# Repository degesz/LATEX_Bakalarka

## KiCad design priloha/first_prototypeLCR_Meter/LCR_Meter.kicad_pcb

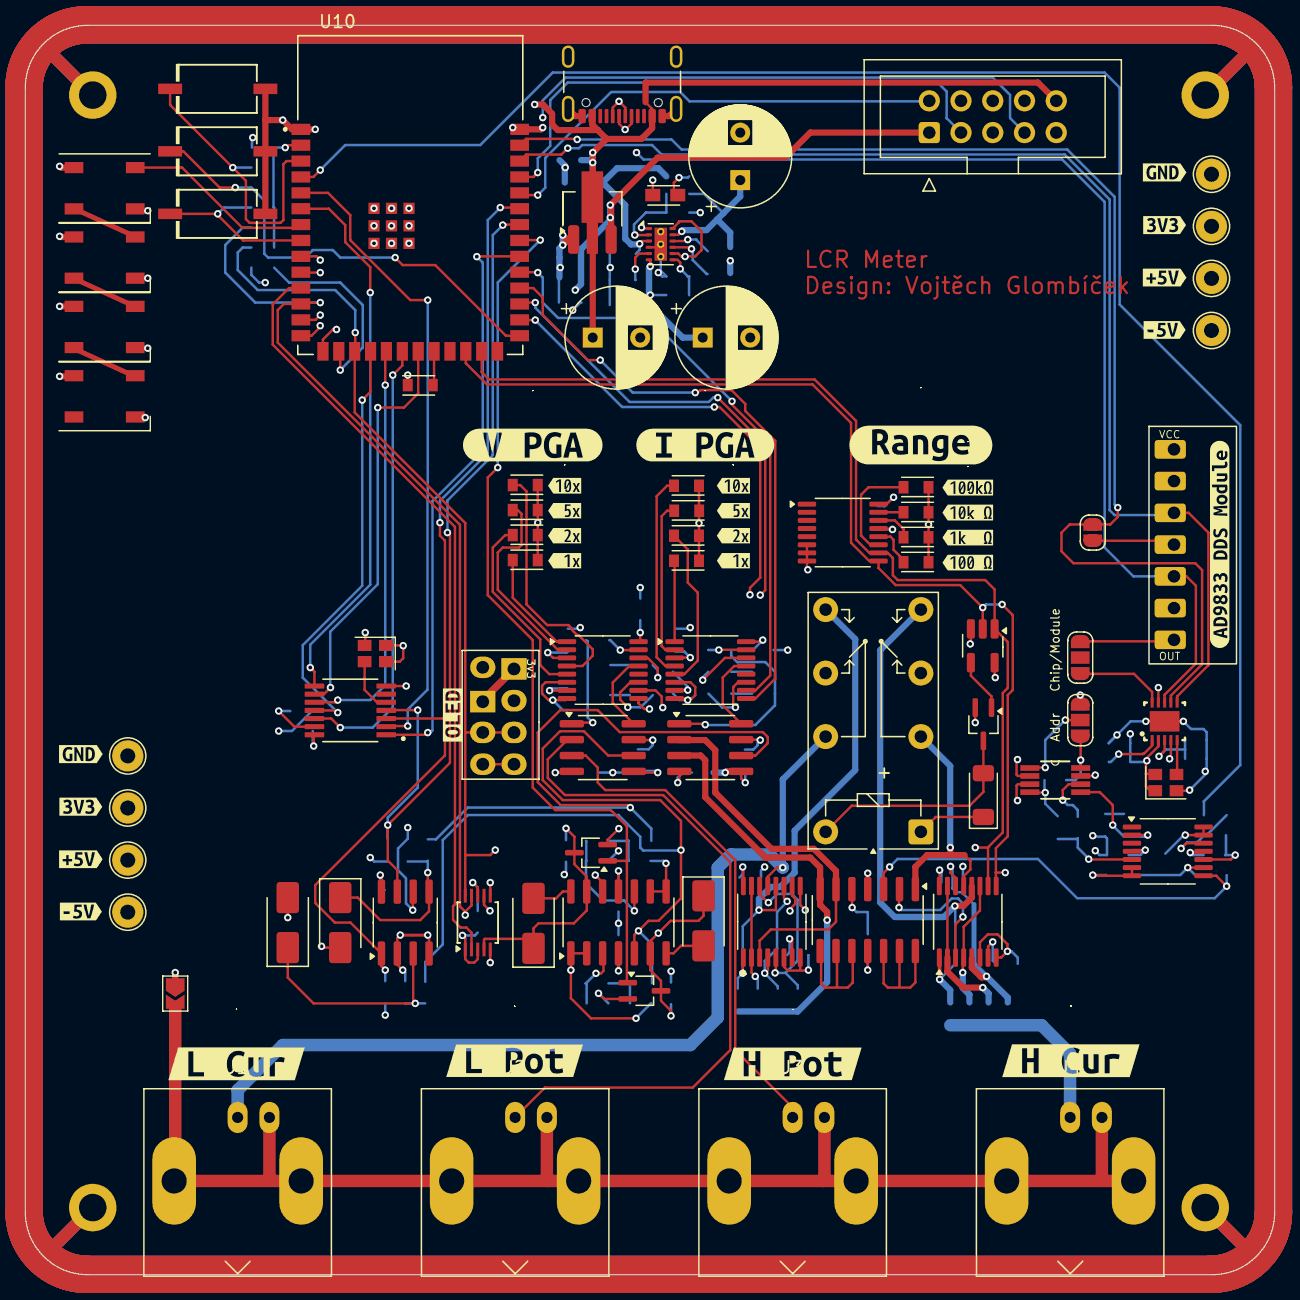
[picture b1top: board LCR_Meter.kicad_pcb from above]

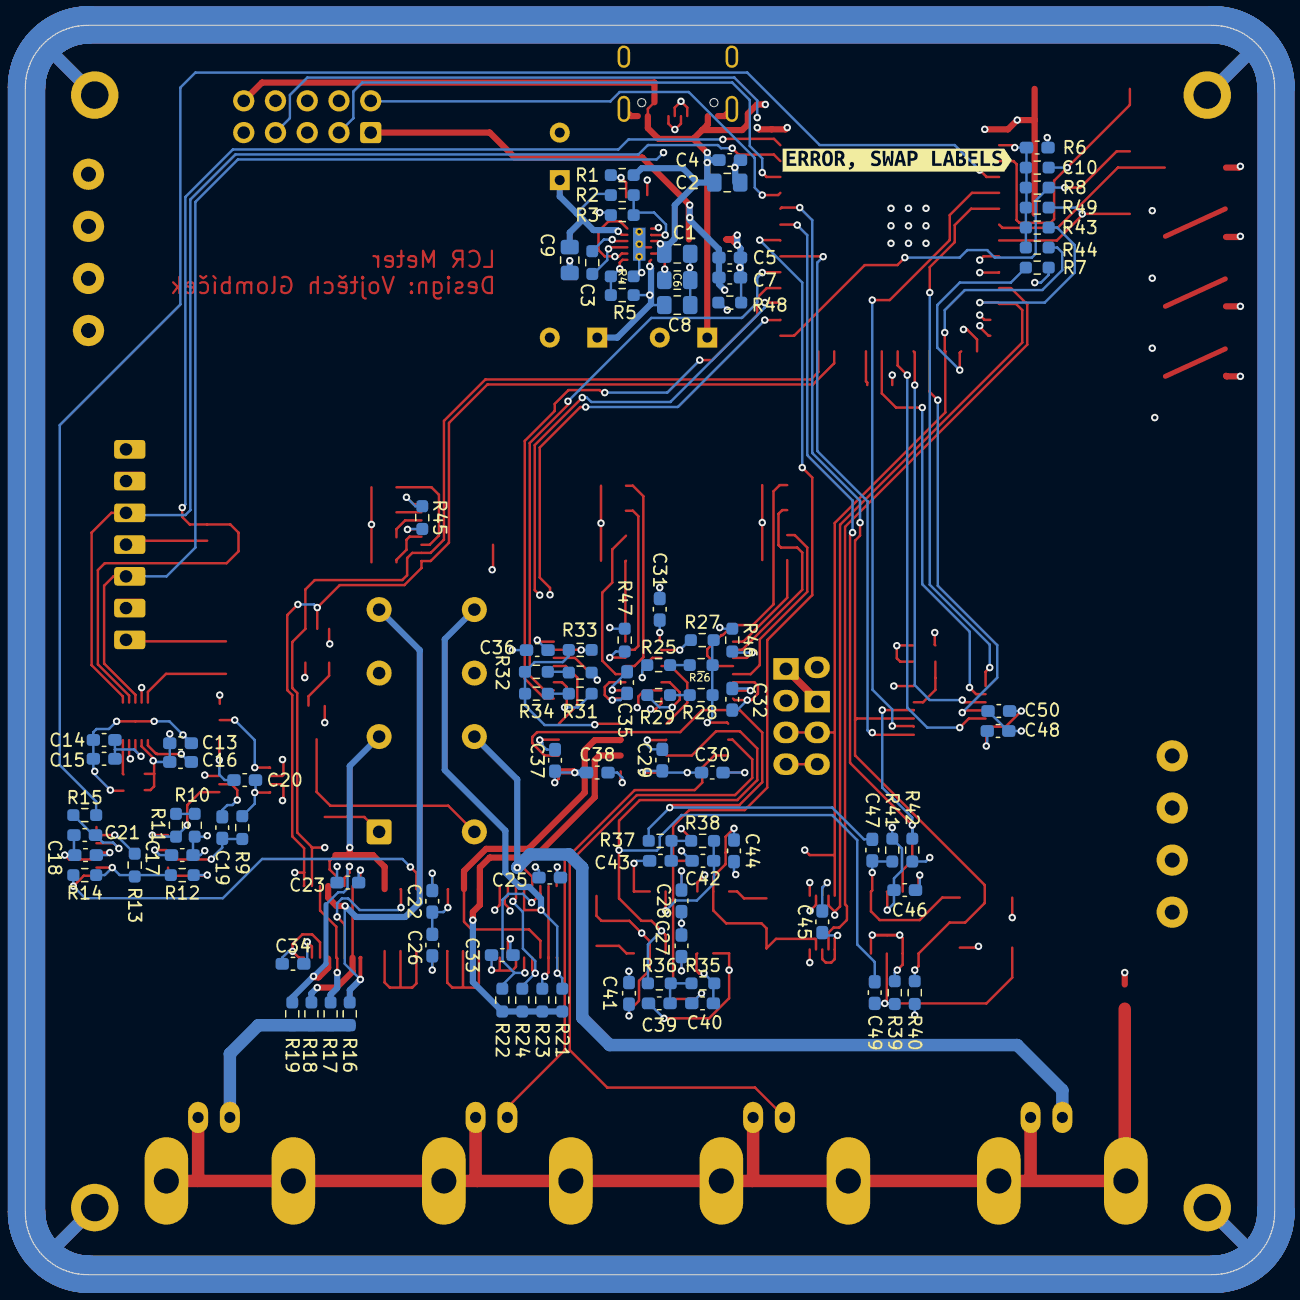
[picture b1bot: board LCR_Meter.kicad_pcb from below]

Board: 6 copper layers, 99.9 x 99.9 mm, 198 parts (96 on the bottom side), 132 nets.

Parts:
 : TestPoint_THTPad_D2.5mm_Drill1.2mm
 #2,  #16: G***; kibuzzard-678FA578
 #3,  #4,  #5,  #6,  #7,  #10,  #14: TestPoint_THTPad_D2.5mm_Drill1.2mm
 #8,  #15: G***; kibuzzard-678FA580
 #9,  #11: G***; kibuzzard-678FA556
 #12,  #13: G***; kibuzzard-678FA586
C1, C2, C6, C8, C9: 4.7u; C_0805_2012Metric_Pad1.18x1.45mm_HandSolder
C3: 1u; R_0603_1608Metric_Pad0.98x0.95mm_HandSolder
C4, C5, C14, C19, C47, C49: 100n; C_0603_1608Metric_Pad1.08x0.95mm_HandSolder
C7, C10, C13, C15, C17, C18, C20, C21, C22, C23, C25, C26, C27, C28, C29, C30, C31, C32, C33, C34, C35, C36, C37, C38, C41, C44, C45, C46, C48, C50: 1u; C_0603_1608Metric_Pad1.08x0.95mm_HandSolder
C11, C12, C51: 470u; CP_Radial_D8.0mm_P3.80mm
C16: 10n; C_0603_1608Metric_Pad1.08x0.95mm_HandSolder
C39, C40, C42, C43: 330n; C_0603_1608Metric_Pad1.08x0.95mm_HandSolder
D1: LED; LED_miniPLCC_2315_Handsoldering
D2: D_Schottky; D_MiniMELF
D3, D4, D5, D6: SS14; D_SMA
D7, D8, D9, D10, D11, D12, D13, D14, D15, D16, D17, D18, D20: LED; LED_miniPLCC_2315
D19, D21, D22, D23: WS2812B; LED_WS2812B_PLCC4_5.0x5.0mm_P3.2mm
J1, J2, J3, J4: Conn_Coaxial; BNC_Amphenol_B6252HB-NPP3G-50_Horizontal
J5: USB_C_Receptacle_USB2.0_16P; USB_C_Receptacle_GCT_USB4105-xx-A_16P_TopMnt_Horizontal
J6: IDC 2x5; IDC-Header_2x05_P2.54mm_Vertical
J7: Display OLED; FanPinHeader_1x04_P2.54mm_Vertical
JP1, JP2: SolderJumper_3_Open; SolderJumper-3_P1.3mm_Open_RoundedPad1.0x1.5mm
JP3: SolderJumper_2_Open; SolderJumper-2_P1.3mm_Open_RoundedPad1.0x1.5mm
JP4: SolderJumper_2_Open; SolderJumper-2_P1.3mm_Open_TrianglePad1.0x1.5mm
K1: Relay_DPDT; Relay_CIT-J104D
Q1, Q2, Q3: NX3008NBK; SOT-323_SC-70_Handsoldering
R1, R6, R7, R8, R19, R22, R40, R42, R45, R46, R47, R48, R49: 1k; R_0603_1608Metric_Pad0.98x0.95mm_HandSolder
R2, R5, R43, R44: 4k7; R_0603_1608Metric_Pad0.98x0.95mm_HandSolder
R3, R4: 1k5; R_0603_1608Metric_Pad0.98x0.95mm_HandSolder
R9, R15, R17, R24, R27, R33, R39, R41: 100k; R_0603_1608Metric_Pad0.98x0.95mm_HandSolder
R10, R12, R13, R14, R18, R23, R35, R36, R37, R38: 10k; R_0603_1608Metric_Pad0.98x0.95mm_HandSolder
R11: 33k; R_0603_1608Metric_Pad0.98x0.95mm_HandSolder
R16, R21: 100R; R_0603_1608Metric_Pad0.98x0.95mm_HandSolder
R25, R29, R30, R31: 0R; R_0603_1608Metric_Pad0.98x0.95mm_HandSolder
R26, R32: 200k; R_0603_1608Metric_Pad0.98x0.95mm_HandSolder
R28, R34: 22k; R_0603_1608Metric_Pad0.98x0.95mm_HandSolder
SW1, SW2, SW3: SW_SPST; SW-SMD_L6.1-W3.7-LS7.9
U1: AD9837; AD9837_AD9837
U2, U5: TLV9154; SOIC-14_3.9x8.7mm_P1.27mm
U3: ADS1115IDGS; TSSOP-10_3x3mm_P0.5mm
U4: LM393; SOIC-8_3.9x4.9mm_P1.27mm
U7: TDC7200PWR; TDC7200PWR_SOP65P640X120-14N
U8: LM27762; WSON-12-1EP_3x2mm_P0.5mm_EP1x2.65_ThermalVias
U9: HT75xx-1-SOT89; SOT-89-3_Handsoldering
U10: ESP32-S2-SOLO-N4; ESP32-S2-SOLO-N4_XCVR_ESP32-S2-SOLO-N4
U12: TL074; TSSOP-14_4.4x5mm_P0.65mm
U13: MCP4561-502E_MS; MCP4561-502E_MS_SOP65P490X110-8N
U14, U16, U18, U20, U23: CD74HC4052; TSSOP-16_4.4x5mm_P0.65mm
U17, U21: INA823; SOIC-8_3.9x4.9mm_P1.27mm
U19: 74LVC1G02; SOT-23-5_HandSoldering
U22: AD9833_Module
X1, X2: SG-210STF; Oscillator_SMD_SeikoEpson_SG210-4Pin_2.5x2.0mm
kibuzzard-67C21963: G***; kibuzzard-67C21963
kibuzzard-678FC3F7: G***; kibuzzard-678FC3F7
kibuzzard-678FC3FC: G***; kibuzzard-678FC3FC
kibuzzard-678FC38E: G***; kibuzzard-678FC38E
kibuzzard-678FC401: G***; kibuzzard-678FC401
kibuzzard-6790BC5C, kibuzzard-6790BC5C#2: G***; kibuzzard-6790BC5C
kibuzzard-6790BC8C, kibuzzard-6790BC8C#2: G***; kibuzzard-6790BC8C
kibuzzard-6790BC71, kibuzzard-6790BC71#2: G***; kibuzzard-6790BC71
kibuzzard-6790BC83, kibuzzard-6790BC83#2: G***; kibuzzard-6790BC83
kibuzzard-6790BCCF: G***; kibuzzard-6790BCCF
kibuzzard-6790BCE4: G***; kibuzzard-6790BCE4
kibuzzard-6790BCFE: G***; kibuzzard-6790BCFE
kibuzzard-6790BDCA: G***; kibuzzard-6790BDCA
kibuzzard-6790BDD8: G***; kibuzzard-6790BDD8
kibuzzard-6790BDEA: G***; kibuzzard-6790BDEA
kibuzzard-6790BDF0: G***; kibuzzard-6790BDF0
kibuzzard-67960D2E: G***; kibuzzard-67960D2E

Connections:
+3V3: .1, #6.1, C5.1, C7.1, C10.2, C13.2, C16.2, C20.2, C45.2, C48.2, J6.1, J7.1, JP1.3 (B), R6.1, R8.1, R40.1, R42.1, R43.1, R44.1, R45.1, R46.1, R47.1, R49.1, U1.P$2 (VDD), U3.8 (VDD), U7.14 (VDD), U9.3 (VOUT), U10.2 (3V3), U13.8 (VDD), U22.1 (VCC), U23.16 (VDD), X1.1 (~ST), X1.4 (Vcc), X2.1 (~ST), X2.4 (Vcc)
+5V: #3.1, #4.1, C9.1, C17.2, C22.2, C23.2, C25.2, C27.2, C29.2, C31.2, C36.2, C37.2, C46.2, C51.1, D2.1 (K), K1.A1, R2.2, U2.4 (V+), U4.8 (V+), U5.4 (V+), U8.11 (OUT+), U12.4 (V+), U14.16 (VDD), U16.16 (VDD), U17.7 (V+), U18.16 (VDD), U19.5 (VCC), U20.16 (VDD), U21.7 (V+)
+5V_USB: C1.1, C2.1, C4.1, C11.1, D19.1 (VDD), D21.1 (VDD), D22.1 (VDD), D23.1 (VDD), J5.A4 (VBUS), J5.A9 (VBUS), J5.B4 (VBUS), J5.B9 (VBUS), J6.10, R1.2, U8.3 (VIN), U8.8 (EN-), U8.12 (EN+), U9.2 (VIN)
-5V: #5.1, #10.1, C8.1, C12.1, C18.2, C26.2, C28.2, C30.2, C32.2, C33.2, C34.2, C35.2, C38.2, R5.2, U2.11 (V-), U5.11 (V-), U8.6 (OUT-), U12.11 (V-), U14.7 (VEE), U16.7 (VEE), U17.4 (V-), U18.7 (VEE), U20.7 (VEE), U21.4 (V-)
/Analog frontend/Sig_IN: R14.2, U2.3 (+), U12.8
/Drive signal source/F_Sync: U1.P$8 (FSYNC), U10.15 (IO3), U22.5 (FSYNC)
/Drive signal source/Offset_PWM: R15.1, U10.4 (IO4)
/Drive signal source/S_Clock: JP3.2 (B), U1.P$7 (SCLK), U10.39 (IO1)
/Drive signal source/S_Data: U1.P$6 (SDATA), U10.38 (IO2), U22.3 (SDATA)
/LEDs/LED_1: D20.2 (A), U10.22 (IO14)
/LEDs/RGB_Data: D19.4 (DIN), U10.7 (IO7)
/Power supply + USB/USB_D+: J5.A6 (D+), J5.B6 (D+), U10.14 (IO20)
/Power supply + USB/USB_D-: J5.A7 (D-), J5.B7 (D-), U10.13 (IO19)
ADC_Alert: U3.2 (ALERT/RDY), U10.11 (IO18)
BNC_Shield: J1.2 (Ext), J2.2 (Ext), J3.2 (Ext), J4.2 (Ext), JP4.2 (B)
GND: #7.1, #14.1, C1.2, C2.2, C4.2, C5.2, C6.2, C7.2, C8.2, C9.2, C10.1, C11.2, C12.2, C13.1, C14.1, C15.1, C17.1, C18.1, C20.1, C21.1, C22.1, C23.1, C25.1, C26.1, C27.1, C28.1, C29.1, C30.1, C31.1, C32.1, C33.1, C34.1, C35.1, C36.1, C37.1, C38.1, C40.2, C41.1, C42.2, C44.1, C45.1, C46.1, C48.1, C50.2, C51.2, D1.1 (K), D5.2 (A), D6.2 (A), D7.1 (K), D8.1 (K), D9.1 (K), D10.1 (K), D11.1 (K), D12.1 (K), D13.1 (K), D14.1 (K), D15.1 (K), D16.1 (K), D17.1 (K), D18.1 (K), D19.3 (VSS), D21.3 (VSS), D22.3 (VSS), D23.3 (VSS), J5.A1 (GND), J5.A12 (GND), J5.B1 (GND), J5.B12 (GND), J5.S1 (SHIELD), J6.5, J6.6, J7.2, JP1.1 (A), JP4.1 (A), Q1.2 (S), Q2.2 (S), Q3.2 (S), R3.2, R4.2, R7.1, R9.2, R10.2, R39.2, R41.2, R48.1, SW1.1 (A), SW2.1 (A), SW3.1 (A), U1.P$0 (DGND), U1.P$4 (DGND), U1.P$9 (AGND), U2.5 (+), U3.1 (ADDR), U3.3 (GND), U4.2 (-), U4.4 (V-), U4.6 (-), U7.7 (GND), U8.1 (PGOOD), U8.4 (GND), U8.13 (PAD), U9.1 (GND), U10.1 (GND), U10.40 (GND), U12.10 (+), U13.4 (VSS), U13.7 (P0B), U14.6 (INH), U14.8 (VSS), U16.6 (INH), U16.8 (VSS), U17.5 (Ref), U18.6 (INH), U18.8 (VSS), U19.3 (GND), U20.6 (INH), U20.8 (VSS), U21.5 (Ref), U22.2 (DGND), U22.6 (AGND), U23.6 (INH), U23.7 (VEE), U23.8 (VSS), X1.2 (GND), X2.2 (GND)
I2C_SCL: J6.9, J7.3, R44.2, U3.10 (SCL), U10.17 (IO9), U13.2 (SCL)
I2C_SDA: J6.8, J7.4, R43.2, U3.9 (SDA), U10.12 (IO8), U13.3 (SDA)
I_Mean: C43.1, U3.5 (AIN1), U5.8, U5.9 (-)
I_PGA_A: U10.31 (IO38), U20.10 (A)
I_PGA_B: U10.30 (IO37), U20.9 (B)
I_Peak: C44.2, D4.1 (K), Q3.3 (D), U3.4 (AIN0), U5.13 (-)
I_Range_A: U10.25 (IO34), U14.10 (A), U16.10 (A), U19.1, U23.10 (A)
I_Range_B: U10.24 (IO33), U14.9 (B), U16.9 (B), U19.2, U23.9 (B)
I_Sens: R21.2, R22.2, R23.2, R24.2, U2.7, U21.3 (+)
I_Square: R42.2, U4.7, U7.4 (STOP), U10.34 (IO41)
unnamed: C39.2, R35.1, R36.2
unnamed: C43.2, R37.2, R38.1
unnamed: D1.2 (A), R1.1
unnamed: D2.2 (A), K1.A2, Q1.3 (D)
unnamed: D3.2 (A), U5.7
unnamed: D4.2 (A), U5.14
unnamed: C49.1, D5.1 (K), R39.1, U4.3 (+)
unnamed: C47.1, D6.1 (K), R41.1, U4.5 (+)
unnamed: D7.2 (A), U23.12 (X0)
unnamed: D8.2 (A), U23.14 (X1)
unnamed: D9.2 (A), U23.15 (X2)
unnamed: D10.2 (A), U23.11 (X3)
unnamed: D11.2 (A), U20.1 (Y0)
unnamed: D12.2 (A), U20.5 (Y1)
unnamed: D13.2 (A), U20.2 (Y2)
unnamed: D14.2 (A), U20.4 (Y3)
unnamed: D15.2 (A), U18.1 (Y0)
unnamed: D16.2 (A), U18.5 (Y1)
unnamed: D17.2 (A), U18.2 (Y2)
unnamed: D18.2 (A), U18.4 (Y3)
unnamed: D19.2 (DOUT), D21.4 (DIN)
unnamed: D20.1 (K), R48.2
unnamed: D21.2 (DOUT), D22.4 (DIN)
unnamed: D22.2 (DOUT), D23.4 (DIN)
unnamed: J2.1 (In), U17.2 (-)
unnamed: J3.1 (In), U17.3 (+)
unnamed: J4.1 (In), R16.2, R17.2, R18.2, R19.2
unnamed: J6.2, U10.36 (RXD0)
unnamed: J6.3, U10.37 (TXD0)
unnamed: J6.4, U10.9 (IO16)
unnamed: J6.7, U10.10 (IO17)
unnamed: JP1.2 (C), U13.1 (HVC/A0)
unnamed: JP2.1 (A), U22.7 (OUT)
unnamed: JP2.3 (B), U1.P$10 (VOUT)
unnamed: JP3.1 (A), U22.4 (SCLK)
unnamed: Q1.1 (G), U19.4
unnamed: R10.1, R11.2
unnamed: R25.2, R26.1
unnamed: R28.1, R29.2
unnamed: R30.2, R32.1
unnamed: R31.2, R34.1
unnamed: R6.2, SW1.2 (B), U10.3 (EN)
unnamed: R8.2, SW2.2 (B), U10.27 (IO0)
unnamed: R49.2, SW3.2 (B), U10.8 (IO15)
unnamed: C14.2, C15.2, U1.P$3 (CAP/2.5V)
unnamed: C16.1, U1.P$1 (COMP)
unnamed: U1.P$5 (MCLK), X1.3 (OUT)
unnamed: U2.8, U2.9 (-), U2.10 (+)
unnamed: U2.12 (+), U2.13 (-), U2.14
unnamed: C40.1, R35.2, U5.3 (+)
unnamed: C49.2, R36.1, U5.5 (+), U17.6
unnamed: C42.1, R38.2, U5.10 (+)
unnamed: C47.2, R37.1, U5.12 (+), U21.6
unnamed: U7.5 (CLOCK), X2.3 (OUT)
unnamed: C50.1, U7.13 (VREG)
unnamed: C3.1, U8.10 (C+)
unnamed: C3.2, U8.9 (C-)
unnamed: C6.1, U8.5 (CP)
unnamed: R2.1, R3.1, U8.2 (FB+)
unnamed: R4.1, R5.1, U8.7 (FB-)
unnamed: R7.2, U10.16 (IO46)
unnamed: R11.1, U12.2 (-), U13.5 (P0A)
unnamed: C19.1, R9.1, U12.5 (+)
unnamed: R12.1, U12.6 (-), U12.7
unnamed: R12.2, R13.2, R14.1, U12.9 (-)
unnamed: C21.2, R15.2, U12.12 (+)
unnamed: R13.1, U12.13 (-), U12.14
unnamed: C19.2, U13.6 (P0W)
unnamed: R19.1, U14.5 (Y1), U14.14 (X1)
unnamed: R18.1, U14.2 (Y2), U14.15 (X2)
unnamed: R17.1, U14.4 (Y3), U14.11 (X3)
unnamed: U2.2 (-), U14.3 (Y)
unnamed: R22.1, U16.5 (Y1), U16.14 (X1)
unnamed: R23.1, U16.2 (Y2), U16.15 (X2)
unnamed: R24.1, U16.4 (Y3), U16.11 (X3)
unnamed: U2.6 (-), U16.3 (Y), U21.2 (-)
unnamed: R25.1, U18.14 (X1)
unnamed: R27.1, U18.15 (X2)
unnamed: R29.1, U18.11 (X3)
unnamed: R46.2, U18.3 (Y)
unnamed: R30.1, U20.14 (X1)
unnamed: R33.1, U20.15 (X2)
unnamed: R31.1, U20.11 (X3)
unnamed: R47.2, U20.3 (Y)
unnamed: R45.2, U23.13 (X)
Peak_Hold_RST: Q2.1 (G), Q3.1 (G), U10.33 (IO40)
Rg_1_A: U17.8 (Rg), U18.13 (X)
Rg_1_B: R26.2, R27.2, R28.2, U17.1 (Rg)
Rg_2_A: U20.13 (X), U21.8 (Rg)
Rg_2_B: R32.2, R33.2, R34.2, U21.1 (Rg)
SW_BYPASS_1_A: K1.11, U2.1, U14.13 (X)
SW_BYPASS_1_B: K1.14, R16.1, U14.1 (Y0), U14.12 (X0)
SW_BYPASS_2_A: J1.1 (In), K1.21, U16.13 (X)
SW_BYPASS_2_B: K1.24, R21.1, U16.1 (Y0), U16.12 (X0)
TDC_!CS: U7.11 (~CS), U10.18 (IO10)
TDC_Enable: U7.1 (ENABLE), U10.32 (IO39)
TDC_Int: U7.2 (TRIGG), U10.5 (IO5)
TDC_MISO: U7.9 (DOUT), U10.21 (IO13)
TDC_MOSI: U7.10 (DIN), U10.19 (IO11)
TDC_SCLK: U7.12 (SCLK), U10.20 (IO12)
TDC_Trig: U7.8 (~INT), U10.6 (IO6)
V_Mean: C39.1, U3.7 (AIN3), U5.1, U5.2 (-)
V_PGA_A: U10.29 (IO36), U18.10 (A)
V_PGA_B: U10.28 (IO35), U18.9 (B)
V_Peak: C41.2, D3.1 (K), Q2.3 (D), U3.6 (AIN2), U5.6 (-)
V_Square: R40.2, U4.1, U7.3 (START), U10.35 (IO42)

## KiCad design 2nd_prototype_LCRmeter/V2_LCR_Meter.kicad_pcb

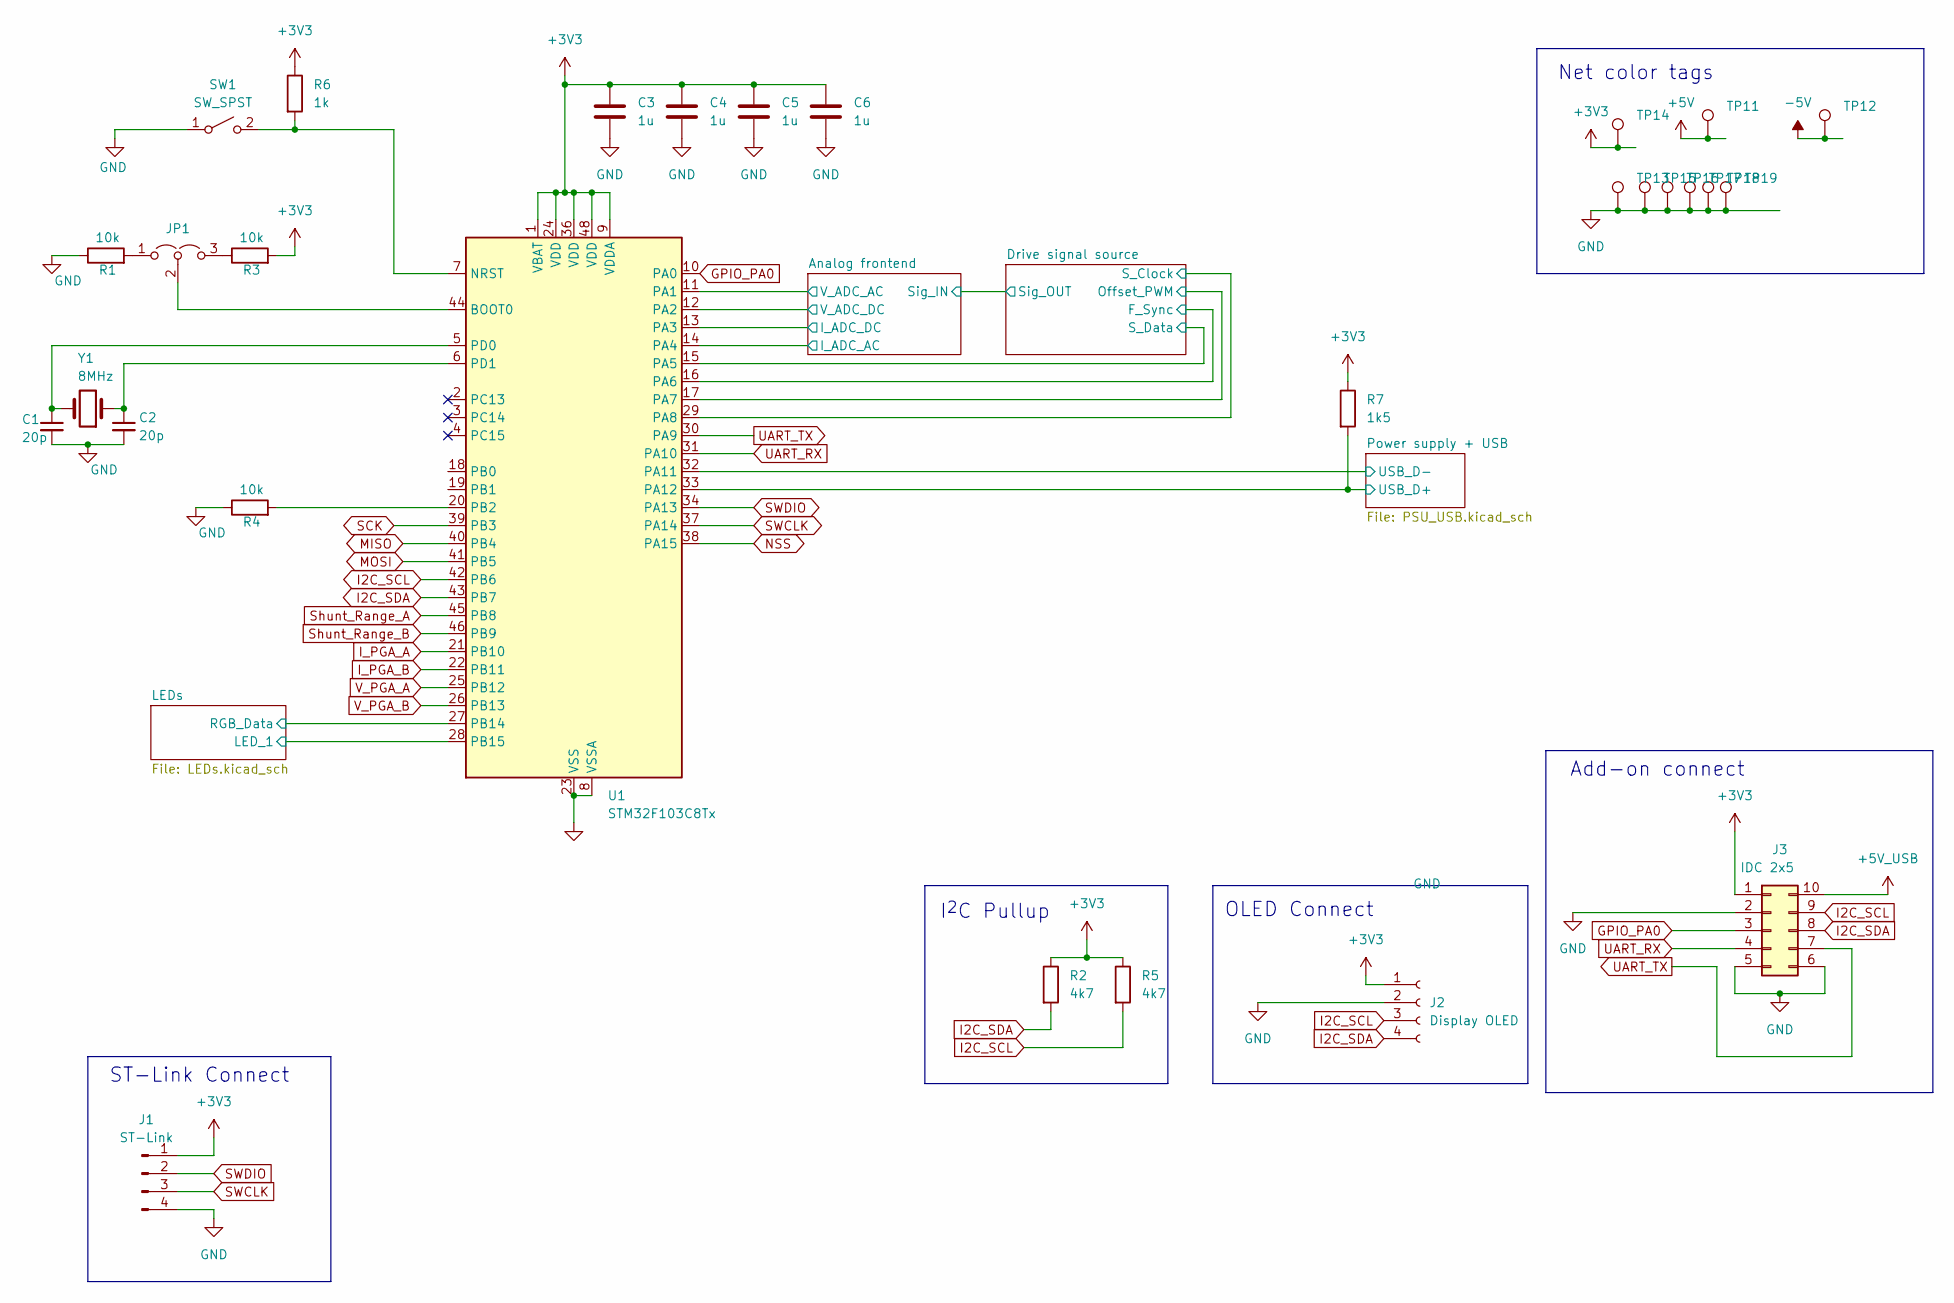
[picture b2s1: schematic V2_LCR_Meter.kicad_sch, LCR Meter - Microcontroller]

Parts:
C1, C2: 20p; C_0603_1608Metric_Pad1.08x0.95mm_HandSolder
C3, C4, C5, C6: 1u; C_0603_1608Metric_Pad1.08x0.95mm_HandSolder
J1: ST-Link; PinHeader_1x04_P2.54mm_Vertical_SMD_Pin1Left
J2: Display OLED; FanPinHeader_1x04_P2.54mm_Vertical
J3: IDC 2x5; IDC-Header_2x05_P2.54mm_Vertical
JP1: Jumper_3_Open; PinHeader_1x03_P2.54mm_Vertical_SMD_Pin1Left
R1, R3, R4: 10k; R_0603_1608Metric_Pad0.98x0.95mm_HandSolder
R2, R5: 4k7; R_0603_1608Metric_Pad0.98x0.95mm_HandSolder
R6: 1k; R_0603_1608Metric_Pad0.98x0.95mm_HandSolder
R7: 1k5; R_0603_1608Metric_Pad0.98x0.95mm_HandSolder
SW1: SW_SPST; SW-SMD_L6.1-W3.7-LS7.9
TP11, TP12, TP13, TP14, TP15, TP16, TP17, TP18, TP19: TestPoint; Pin_D1.0mm_L10.0mm
U1: STM32F103C8Tx; LQFP-48_7x7mm_P0.5mm
Y1: 8MHz; Crystal_HC49-U_Vertical

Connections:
+3V3: C3.2, C4.2, C5.2, C6.2, J1.1, J2.1, J3.1, R2.1, R3.2, R5.1, R6.1, R7.1, TP14.1, U1.1 (VBAT), U1.9 (VDDA), U1.24 (VDD), U1.36 (VDD), U1.48 (VDD); also elsewhere on the board
+5V: TP11.1; also elsewhere on the board
+5V_USB: J3.10; also elsewhere on the board
-5V: TP12.1; also elsewhere on the board
/Analog frontend/I_HighPass: U1.14 (PA4); also elsewhere on the board
/Analog frontend/I_LowPass: U1.13 (PA3); also elsewhere on the board
/Analog frontend/V_HighPass: U1.11 (PA1); also elsewhere on the board
/Analog frontend/V_LowPass: U1.12 (PA2); also elsewhere on the board
/Drive signal source/F_Sync: U1.16 (PA6); also elsewhere on the board
/Drive signal source/Offset_PWM: U1.17 (PA7); also elsewhere on the board
/Drive signal source/S_Clock: U1.29 (PA8); also elsewhere on the board
/Drive signal source/S_Data: U1.15 (PA5); also elsewhere on the board
/LEDs/LED_1: U1.28 (PB15); also elsewhere on the board
/LEDs/RGB_Data: U1.27 (PB14); also elsewhere on the board
/Power supply + USB/USB_D+: R7.2, U1.33 (PA12); also elsewhere on the board
/Power supply + USB/USB_D-: U1.32 (PA11); also elsewhere on the board
GND: C1.2, C2.2, C3.1, C4.1, C5.1, C6.1, J1.4, J2.2, J3.2, J3.5, J3.6, R1.1, R4.1, SW1.1 (A), TP13.1, TP15.1, TP16.1, TP17.1, TP18.1, TP19.1, U1.8 (VSSA), U1.23 (VSS), U1.35 (VSS), U1.47 (VSS); also elsewhere on the board
GPIO_PA0: J3.3, U1.10 (PA0)
I2C_SCL: J2.3, J3.9, R5.2, U1.42 (PB6); also elsewhere on the board
I2C_SDA: J2.4, J3.8, R2.2, U1.43 (PB7); also elsewhere on the board
I_PGA_A: U1.21 (PB10); also elsewhere on the board
I_PGA_B: U1.22 (PB11); also elsewhere on the board
MISO: U1.40 (PB4)
MOSI: U1.41 (PB5)
NSS: U1.38 (PA15)
unnamed: JP1.1 (A), R1.2
unnamed: JP1.3 (B), R3.1
unnamed: JP1.2 (C), U1.44 (BOOT0)
unnamed: R6.2, SW1.2 (B), U1.7 (NRST)
unnamed: R4.2, U1.20 (PB2)
unnamed: C1.1, U1.5 (PD0), Y1.2
unnamed: C2.1, U1.6 (PD1), Y1.1
SCK: U1.39 (PB3)
SWCLK: J1.3, U1.37 (PA14)
SWDIO: J1.2, U1.34 (PA13)
Shunt_Range_A: U1.45 (PB8); also elsewhere on the board
Shunt_Range_B: U1.46 (PB9); also elsewhere on the board
UART_RX: J3.4, U1.31 (PA10)
UART_TX: J3.7, U1.30 (PA9)
V_PGA_A: U1.25 (PB12); also elsewhere on the board
V_PGA_B: U1.26 (PB13); also elsewhere on the board

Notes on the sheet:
ST-Link Connect
Net color tags
OLED Connect
I^{2}C Pullup
Add-on connect

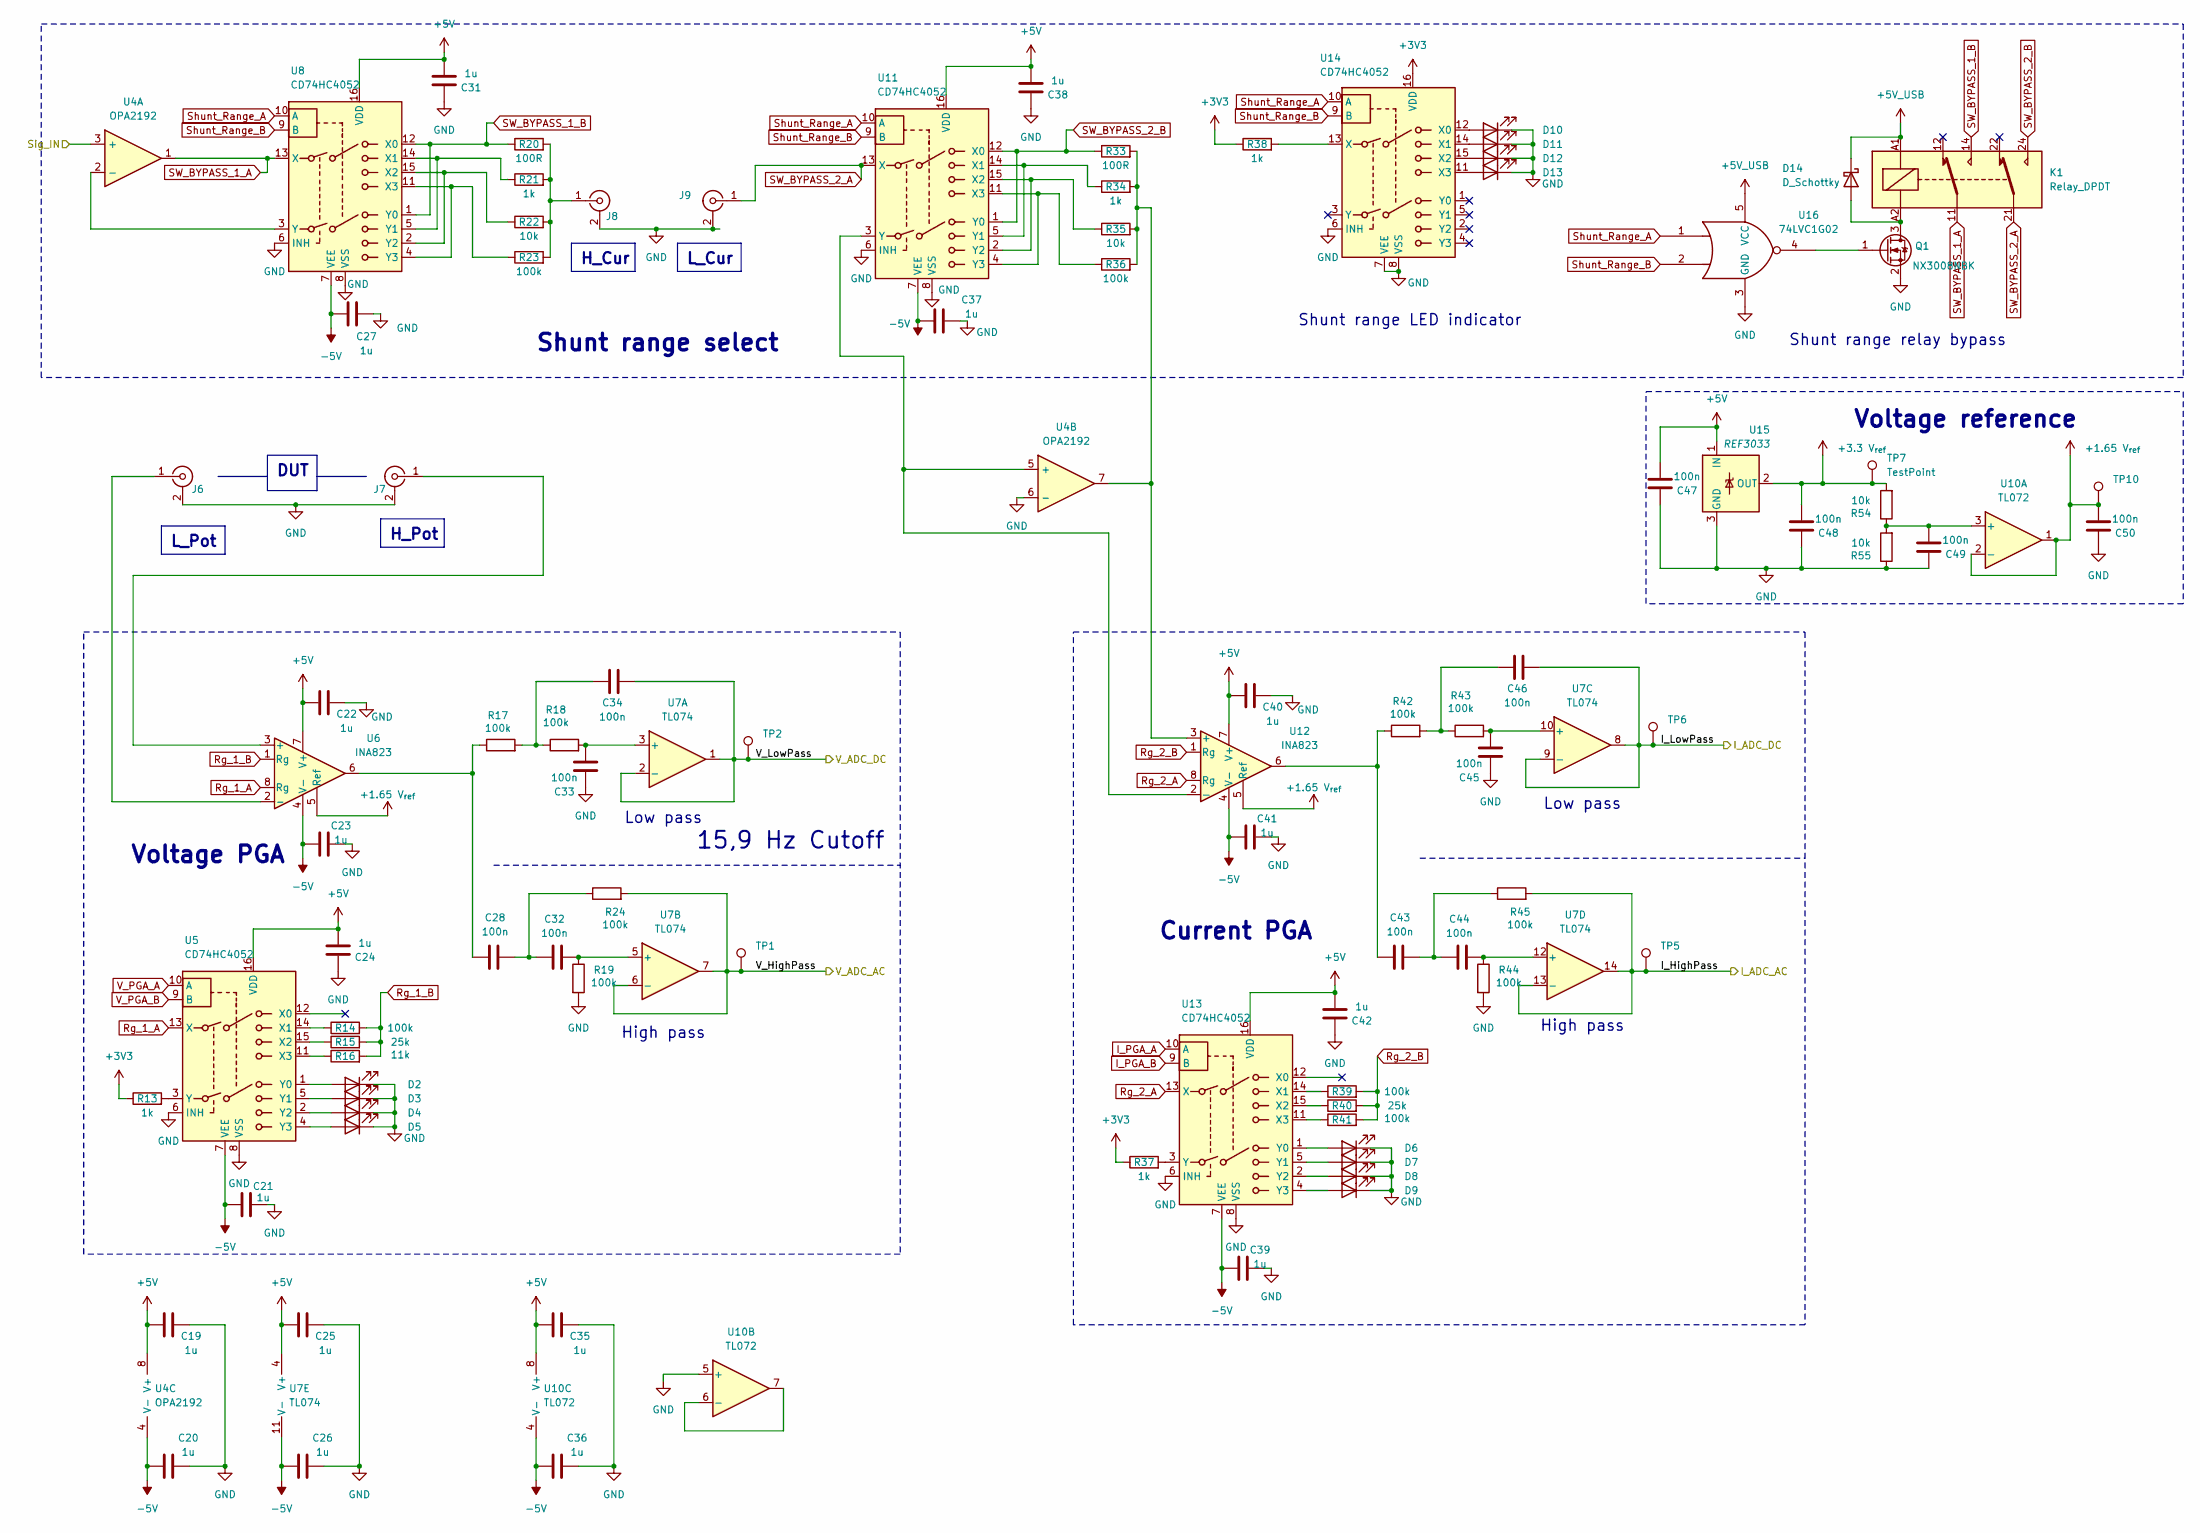
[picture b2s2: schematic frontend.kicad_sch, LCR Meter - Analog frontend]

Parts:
C19, C20, C21, C22, C23, C24, C25, C26, C27, C31, C35, C36, C37, C38, C39, C40, C41, C42: 1u; C_0603_1608Metric_Pad1.08x0.95mm_HandSolder
C28, C32, C33, C34, C43, C44, C45, C46, C47, C48, C49, C50: 100n; C_0603_1608Metric_Pad1.08x0.95mm_HandSolder
D2, D3, D4, D5, D6, D7, D8, D9, D10, D11, D12, D13: LED; LED_miniPLCC_2315
D14: D_Schottky; D_MiniMELF
J6, J7, J8, J9: Conn_Coaxial; BNC_Gold
K1: Relay_DPDT; Relay_DPDT_Finder_30.22
Q1: NX3008NBK; SOT-323_SC-70_Handsoldering
R13, R21, R34, R37, R38: 1k; R_0603_1608Metric_Pad0.98x0.95mm_HandSolder
R14, R17, R18, R19, R23, R24, R36, R39, R41, R42, R43, R44, R45: 100k; R_0603_1608Metric_Pad0.98x0.95mm_HandSolder
R15, R40: 25k; R_0603_1608Metric_Pad0.98x0.95mm_HandSolder
R16: 11k; R_0603_1608Metric_Pad0.98x0.95mm_HandSolder
R20, R33: 100R; R_0603_1608Metric_Pad0.98x0.95mm_HandSolder
R22, R35, R54, R55: 10k; R_0603_1608Metric_Pad0.98x0.95mm_HandSolder
TP1, TP2, TP5, TP6, TP7, TP10: TestPoint; Pin_D1.0mm_L10.0mm
U4: OPA2192; SOIC-8_3.9x4.9mm_P1.27mm
U5, U8, U11, U13, U14: CD74HC4052; TSSOP-16_4.4x5mm_P0.65mm
U6, U12: INA823; SOIC-8_3.9x4.9mm_P1.27mm
U7: TL074; TSSOP-14_4.4x5mm_P0.65mm
U10: TL072; SOIC-8_3.9x4.9mm_P1.27mm
U15: REF3033; SOT-23
U16: 74LVC1G02; SOT-23-5_HandSoldering

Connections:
+1.65 V_{ref}: C50.2, TP10.1, U6.5 (Ref), U10.1, U10.2 (-), U12.5 (Ref)
+3.3 V_{ref}: C48.2, R54.2, TP7.1, U15.2 (OUT)
+3V3: R13.1, R37.1, R38.1, U14.16 (VDD); also elsewhere on the board
+5V: C19.2, C22.2, C24.2, C25.2, C31.2, C35.2, C38.2, C40.2, C42.2, C47.2, U4.8 (V+), U5.16 (VDD), U6.7 (V+), U7.4 (V+), U8.16 (VDD), U10.8 (V+), U11.16 (VDD), U12.7 (V+), U13.16 (VDD), U15.1 (IN); also elsewhere on the board
+5V_USB: D14.1 (K), K1.A1, U16.5 (VCC); also elsewhere on the board
-5V: C20.2, C21.2, C23.2, C26.2, C27.2, C36.2, C37.2, C39.2, C41.2, U4.4 (V-), U5.7 (VEE), U6.4 (V-), U7.11 (V-), U8.7 (VEE), U10.4 (V-), U11.7 (VEE), U12.4 (V-), U13.7 (VEE); also elsewhere on the board
/Analog frontend/I_HighPass: R45.2, TP5.1, U7.13 (-), U7.14; also elsewhere on the board
/Analog frontend/I_LowPass: C46.1, TP6.1, U7.8, U7.9 (-); also elsewhere on the board
/Analog frontend/Sig_IN: U4.3 (+); also elsewhere on the board
/Analog frontend/V_HighPass: R24.2, TP1.1, U7.6 (-), U7.7; also elsewhere on the board
/Analog frontend/V_LowPass: C34.1, TP2.1, U7.1, U7.2 (-); also elsewhere on the board
GND: C19.1, C20.1, C21.1, C22.1, C23.1, C24.1, C25.1, C26.1, C27.1, C31.1, C33.2, C35.1, C36.1, C37.1, C38.1, C39.1, C40.1, C41.1, C42.1, C45.2, C47.1, C48.1, C49.1, C50.1, D2.1 (K), D3.1 (K), D4.1 (K), D5.1 (K), D6.1 (K), D7.1 (K), D8.1 (K), D9.1 (K), D10.1 (K), D11.1 (K), D12.1 (K), D13.1 (K), J6.2 (Ext), J7.2 (Ext), J8.2 (Ext), J9.2 (Ext), Q1.2 (S), R19.2, R44.2, R55.1, U4.6 (-), U5.6 (INH), U5.8 (VSS), U8.6 (INH), U8.8 (VSS), U10.5 (+), U11.6 (INH), U11.8 (VSS), U13.6 (INH), U13.8 (VSS), U14.6 (INH), U14.7 (VEE), U14.8 (VSS), U15.3 (GND), U16.3 (GND); also elsewhere on the board
I_PGA_A: U13.10 (A); also elsewhere on the board
I_PGA_B: U13.9 (B); also elsewhere on the board
unnamed: C28.1, C32.2, R24.1
unnamed: C28.2, R17.1, U6.6
unnamed: C34.2, R17.2, R18.1
unnamed: C43.1, C44.2, R45.1
unnamed: C43.2, R42.1, U12.6
unnamed: C46.2, R42.2, R43.1
unnamed: D2.2 (A), U5.1 (Y0)
unnamed: D3.2 (A), U5.5 (Y1)
unnamed: D4.2 (A), U5.2 (Y2)
unnamed: D5.2 (A), U5.4 (Y3)
unnamed: D6.2 (A), U13.1 (Y0)
unnamed: D7.2 (A), U13.5 (Y1)
unnamed: D8.2 (A), U13.2 (Y2)
unnamed: D9.2 (A), U13.4 (Y3)
unnamed: D10.2 (A), U14.12 (X0)
unnamed: D11.2 (A), U14.14 (X1)
unnamed: D12.2 (A), U14.15 (X2)
unnamed: D13.2 (A), U14.11 (X3)
unnamed: D14.2 (A), K1.A2, Q1.3 (D)
unnamed: J6.1 (In), U6.2 (-)
unnamed: J7.1 (In), U6.3 (+)
unnamed: J8.1 (In), R20.2, R21.2, R22.2, R23.2
unnamed: Q1.1 (G), U16.4
unnamed: U4.2 (-), U8.3 (Y)
unnamed: R14.1, U5.14 (X1)
unnamed: R15.1, U5.15 (X2)
unnamed: R16.1, U5.11 (X3)
unnamed: R13.2, U5.3 (Y)
unnamed: C33.1, R18.2, U7.3 (+)
unnamed: C32.1, R19.1, U7.5 (+)
unnamed: C45.1, R43.2, U7.10 (+)
unnamed: C44.1, R44.1, U7.12 (+)
unnamed: R21.1, U8.5 (Y1), U8.14 (X1)
unnamed: R22.1, U8.2 (Y2), U8.15 (X2)
unnamed: R23.1, U8.4 (Y3), U8.11 (X3)
unnamed: C49.2, R54.1, R55.2, U10.3 (+)
unnamed: U10.6 (-), U10.7
unnamed: R34.1, U11.5 (Y1), U11.14 (X1)
unnamed: R35.1, U11.2 (Y2), U11.15 (X2)
unnamed: R36.1, U11.4 (Y3), U11.11 (X3)
unnamed: U4.5 (+), U11.3 (Y), U12.2 (-)
unnamed: R33.2, R34.2, R35.2, R36.2, U4.7, U12.3 (+)
unnamed: R39.1, U13.14 (X1)
unnamed: R40.1, U13.15 (X2)
unnamed: R41.1, U13.11 (X3)
unnamed: R37.2, U13.3 (Y)
unnamed: R38.2, U14.13 (X)
Rg_1_A: U5.13 (X), U6.8 (Rg)
Rg_1_B: R14.2, R15.2, R16.2, U6.1 (Rg)
Rg_2_A: U12.8 (Rg), U13.13 (X)
Rg_2_B: R39.2, R40.2, R41.2, U12.1 (Rg)
SW_BYPASS_1_A: K1.11, U4.1, U8.13 (X)
SW_BYPASS_1_B: K1.14, R20.1, U8.1 (Y0), U8.12 (X0)
SW_BYPASS_2_A: J9.1 (In), K1.21, U11.13 (X)
SW_BYPASS_2_B: K1.24, R33.1, U11.1 (Y0), U11.12 (X0)
Shunt_Range_A: U8.10 (A), U11.10 (A), U14.10 (A), U16.1; also elsewhere on the board
Shunt_Range_B: U8.9 (B), U11.9 (B), U14.9 (B), U16.2; also elsewhere on the board
V_PGA_A: U5.10 (A); also elsewhere on the board
V_PGA_B: U5.9 (B); also elsewhere on the board

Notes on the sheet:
Low pass
High pass
Current PGA
Shunt range select
Shunt range relay bypass
Voltage reference
Voltage PGA
15,9 Hz Cutoff
Shunt range LED indicator
H_Pot
H_Cur
L_Pot
DUT
L_Cur

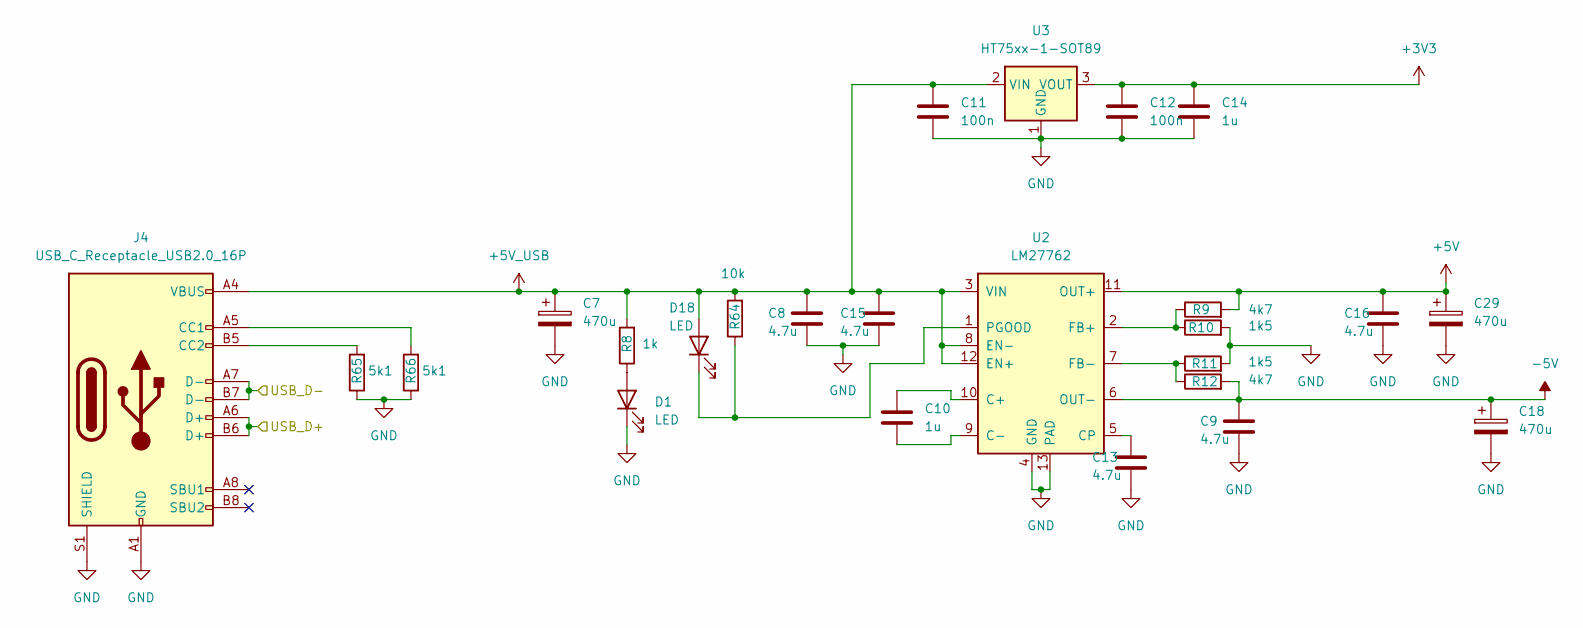
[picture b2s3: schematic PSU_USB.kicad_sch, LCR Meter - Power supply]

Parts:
C7, C18, C29: 470u; CP_EIA-7343-30_AVX-N_HandSolder
C8, C9, C13, C15, C16: 4.7u; C_0603_1608Metric
C10: 1u; R_0603_1608Metric_Pad0.98x0.95mm_HandSolder
C11, C12: 100n; C_0603_1608Metric_Pad1.08x0.95mm_HandSolder
C14: 1u; C_0603_1608Metric_Pad1.08x0.95mm_HandSolder
D1, D18: LED; LED_miniPLCC_2315_Handsoldering
J4: USB_C_Receptacle_USB2.0_16P; USB_C_Receptacle_GCT_USB4105-xx-A_16P_TopMnt_Horizontal
R8: 1k; R_0603_1608Metric_Pad0.98x0.95mm_HandSolder
R9, R12: 4k7; R_0603_1608Metric_Pad0.98x0.95mm_HandSolder
R10, R11: 1k5; R_0603_1608Metric_Pad0.98x0.95mm_HandSolder
R64: 10k; R_0603_1608Metric_Pad0.98x0.95mm_HandSolder
R65, R66: 5k1; R_0603_1608Metric_Pad0.98x0.95mm_HandSolder
U2: LM27762; WSON-12-1EP_3x2mm_P0.5mm_EP1x2.65_ThermalVias
U3: HT75xx-1-SOT89; SOT-89-3_Handsoldering

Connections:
+3V3: C12.1, C14.1, U3.3 (VOUT); also elsewhere on the board
+5V: C16.1, C29.1, R9.2, U2.11 (OUT+); also elsewhere on the board
+5V_USB: C7.1, C8.1, C11.1, C15.1, D18.2 (A), J4.A4 (VBUS), J4.A9 (VBUS), J4.B4 (VBUS), J4.B9 (VBUS), R8.2, R64.2, U2.3 (VIN), U2.8 (EN-), U2.12 (EN+), U3.2 (VIN); also elsewhere on the board
-5V: C9.1, C18.1, R12.2, U2.6 (OUT-); also elsewhere on the board
/Power supply + USB/USB_D+: J4.A6 (D+), J4.B6 (D+); also elsewhere on the board
/Power supply + USB/USB_D-: J4.A7 (D-), J4.B7 (D-); also elsewhere on the board
GND: C7.2, C8.2, C9.2, C11.2, C12.2, C13.2, C14.2, C15.2, C16.2, C18.2, C29.2, D1.1 (K), J4.A1 (GND), J4.A12 (GND), J4.B1 (GND), J4.B12 (GND), J4.S1 (SHIELD), R10.2, R11.2, R65.1, R66.1, U2.4 (GND), U2.13 (PAD), U3.1 (GND); also elsewhere on the board
unnamed: D1.2 (A), R8.1
unnamed: D18.1 (K), R64.1, U2.1 (PGOOD)
unnamed: J4.A5 (CC1), R66.2
unnamed: J4.B5 (CC2), R65.2
unnamed: C10.1, U2.10 (C+)
unnamed: C10.2, U2.9 (C-)
unnamed: C13.1, U2.5 (CP)
unnamed: R9.1, R10.1, U2.2 (FB+)
unnamed: R11.1, R12.1, U2.7 (FB-)
